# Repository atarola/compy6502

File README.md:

# compy6502

`compy6502` is an early-stage 6502 homebrew computer project. The long-term
goal is to build enough hardware and firmware to run Tetris on the machine.

The design follows the spirit of Ben Eater-style breadboard/modular 6502
systems for simplicity and debuggability, but uses a different memory map based
on the MMU/address-decoder architecture in `docs/mmu.png`.

The repo currently includes KiCad hardware designs, early ROM bring-up
firmware, build/write scripts, emulator test scaffolding, and architecture
reference images in `docs/`.

## Memory Map

The intended memory map is:

```text
$0000-$BFFF  RAM
$C000-$C0FF  I/O page
$C100-$FFFF  ROM
```

The I/O page is split into four 64-byte device slots:

```text
$C000-$C03F  IO0B
$C040-$C07F  IO1B
$C080-$C0BF  IO2B
$C0C0-$C0FF  IO3B
```

The linker script currently uses `$8000-$FFFF` as the 32 KB EEPROM image range
so CPU addresses map directly to the correct physical offsets on the chip.

## ROM Layout

The intended ROM organization is:

```text
$C100-$C1FF  public jump table
$C200-$DFFF  kernel routines and drivers
$E000-$EFFF  enhanced monitor
$F500-$FFF9  Wozmon fallback monitor
$FFFA-$FFFF  CPU vectors
```

## Credits

- `docs/mmu.png`: Mike McLaren, K8LH.
- `docs/Beater 02b.png`: Mike McLaren, K8LH.

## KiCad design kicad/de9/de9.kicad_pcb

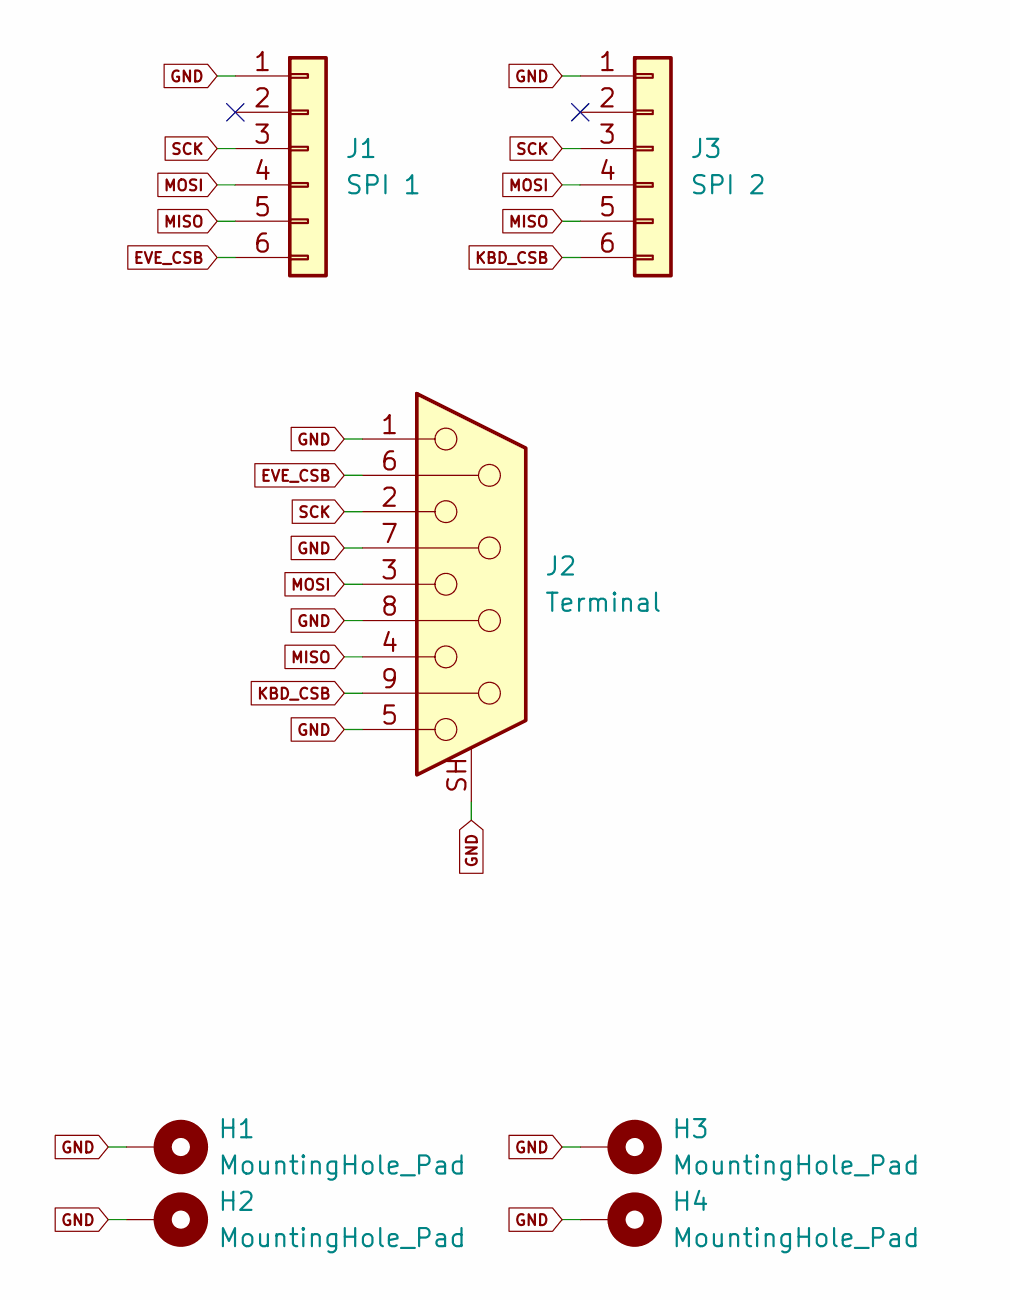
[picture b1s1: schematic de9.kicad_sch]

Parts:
H1, H2, H3, H4: MountingHole_Pad; MountingHole_2.2mm_M2_Pad
J1: SPI 1; JST_XH_B6B-XH-AM_1x06_P2.50mm_Vertical
J2: Terminal; DSUB-9_Pins_Horizontal_P2.77x2.84mm_EdgePinOffset4.94mm_Hou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
J3: SPI 2; JST_XH_B6B-XH-AM_1x06_P2.50mm_Vertical

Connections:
EVE_CSB: J1.6, J2.6
GND: H1.1 (1_1), H2.1 (1_1), H3.1 (1_1), H4.1 (1_1), J1.1, J2.1, J2.5, J2.7, J2.8, J2.SH (PAD), J3.1
KBD_CSB: J2.9, J3.6
MISO: J1.5, J2.4, J3.5
MOSI: J1.4, J2.3, J3.4
SCK: J1.3, J2.2, J3.3

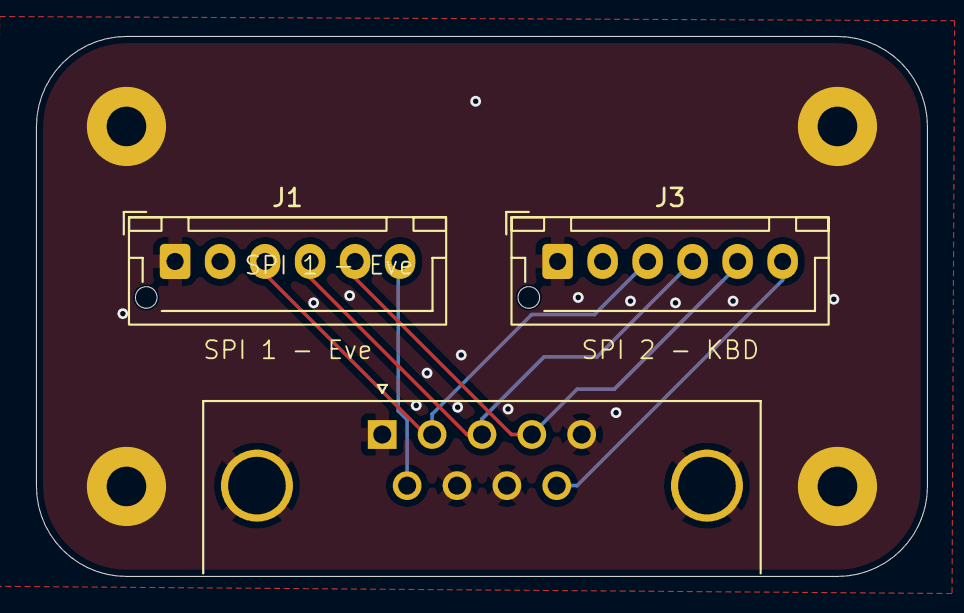
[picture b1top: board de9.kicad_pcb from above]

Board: 2 copper layers, 49.5 x 30.0 mm, 7 parts (0 on the bottom side), 6 nets.

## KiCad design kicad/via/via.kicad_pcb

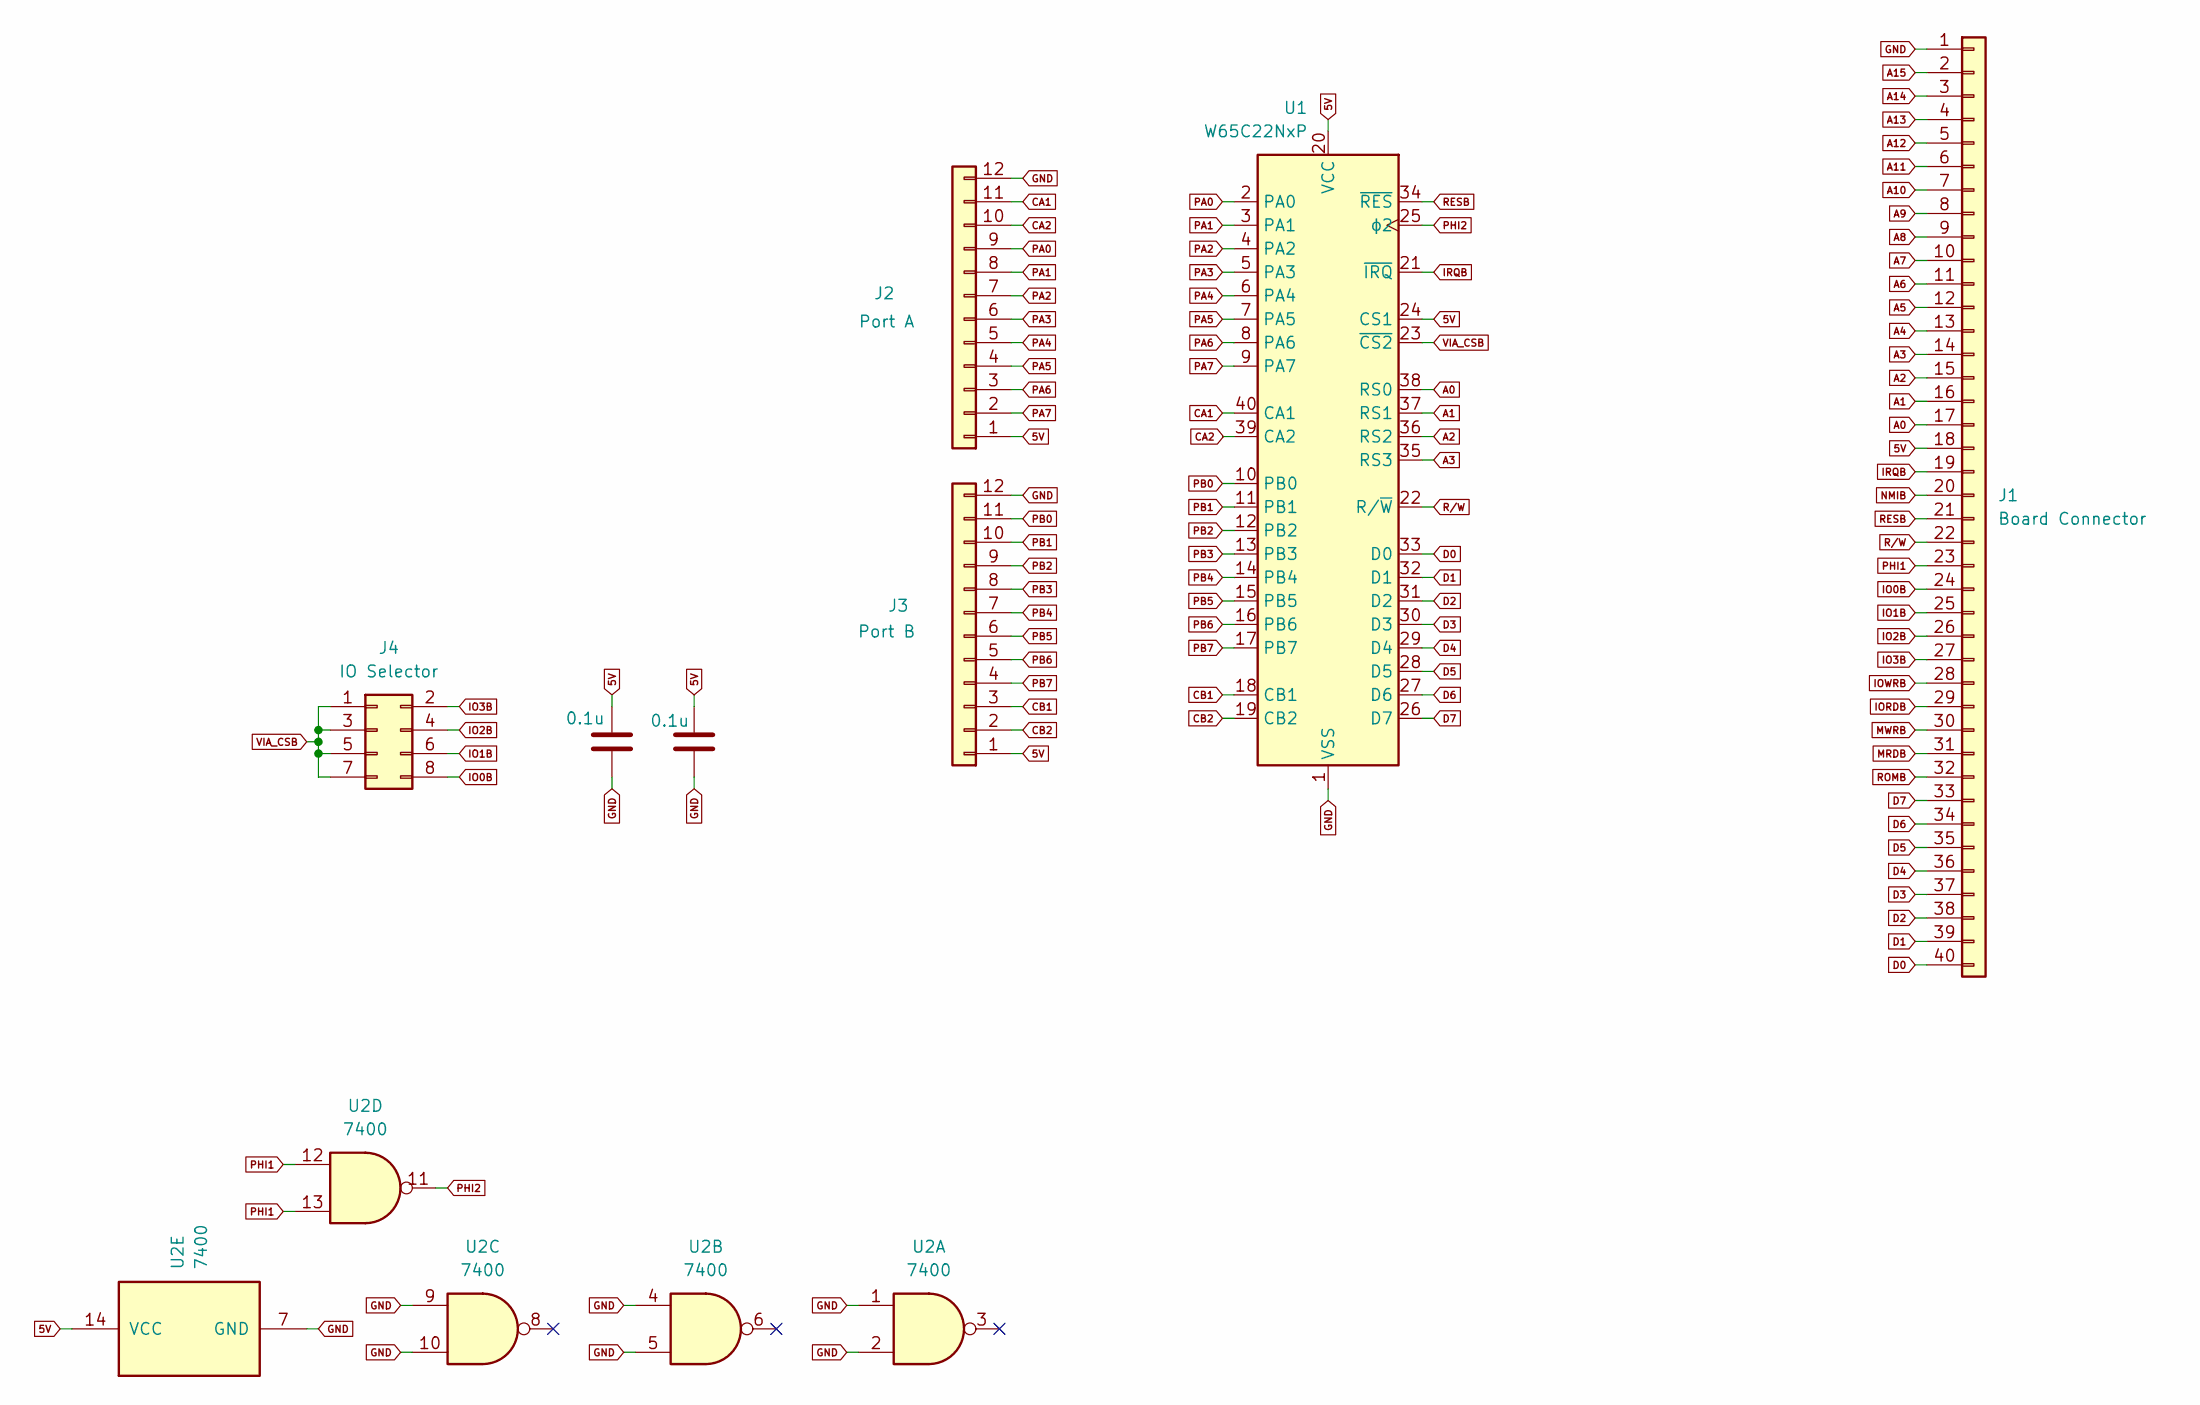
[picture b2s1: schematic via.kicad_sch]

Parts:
C1, C2: 0.1u; C_Disc_D3.0mm_W1.6mm_P2.50mm
J1: Board Connector; PinHeader_1x40_P2.54mm_Horizontal
J2: Port A; PinHeader_1x12_P2.00mm_Horizontal
J3: Port B; PinHeader_1x12_P2.00mm_Horizontal
J4: IO Selector; PinHeader_2x04_P2.54mm_Vertical
U1: W65C22NxP; DIP-40_W15.24mm_Socket_LongPads
U2: 7400; DIP-14_W7.62mm_Socket_LongPads

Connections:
5V: C1.1, C2.1, J1.18, J2.1, J3.1, U1.20 (VCC), U1.24 (CS1), U2.14 (VCC)
A0: J1.17, U1.38 (RS0)
A1: J1.16, U1.37 (RS1)
A2: J1.15, U1.36 (RS2)
A3: J1.14, U1.35 (RS3)
A4: J1.13
A5: J1.12
A6: J1.11
A7: J1.10
A8: J1.9
A9: J1.8
A10: J1.7
A11: J1.6
A12: J1.5
A13: J1.4
A14: J1.3
A15: J1.2
CA1: J2.11, U1.40 (CA1)
CA2: J2.10, U1.39 (CA2)
CB1: J3.3, U1.18 (CB1)
CB2: J3.2, U1.19 (CB2)
D0: J1.40, U1.33 (D0)
D1: J1.39, U1.32 (D1)
D2: J1.38, U1.31 (D2)
D3: J1.37, U1.30 (D3)
D4: J1.36, U1.29 (D4)
D5: J1.35, U1.28 (D5)
D6: J1.34, U1.27 (D6)
D7: J1.33, U1.26 (D7)
GND: C1.2, C2.2, J1.1, J2.12, J3.12, U1.1 (VSS), U2.1, U2.2, U2.4, U2.5, U2.7 (GND), U2.9, U2.10
IO0B: J1.24, J4.8
IO1B: J1.25, J4.6
IO2B: J1.26, J4.4
IO3B: J1.27, J4.2
IORDB: J1.29
IOWRB: J1.28
IRQB: J1.19, U1.21 (~IRQ)
MRDB: J1.31
MWRB: J1.30
NMIB: J1.20
PA0: J2.9, U1.2 (PA0)
PA1: J2.8, U1.3 (PA1)
PA2: J2.7, U1.4 (PA2)
PA3: J2.6, U1.5 (PA3)
PA4: J2.5, U1.6 (PA4)
PA5: J2.4, U1.7 (PA5)
PA6: J2.3, U1.8 (PA6)
PA7: J2.2, U1.9 (PA7)
PB0: J3.11, U1.10 (PB0)
PB1: J3.10, U1.11 (PB1)
PB2: J3.9, U1.12 (PB2)
PB3: J3.8, U1.13 (PB3)
PB4: J3.7, U1.14 (PB4)
PB5: J3.6, U1.15 (PB5)
PB6: J3.5, U1.16 (PB6)
PB7: J3.4, U1.17 (PB7)
PHI1: J1.23, U2.12, U2.13
PHI2: U1.25 (ϕ2), U2.11
RESB: J1.21, U1.34 (~RES)
ROMB: J1.32
R/W: J1.22, U1.22 (R/~W)
VIA_CSB: J4.1, J4.3, J4.5, J4.7, U1.23 (~CS2)

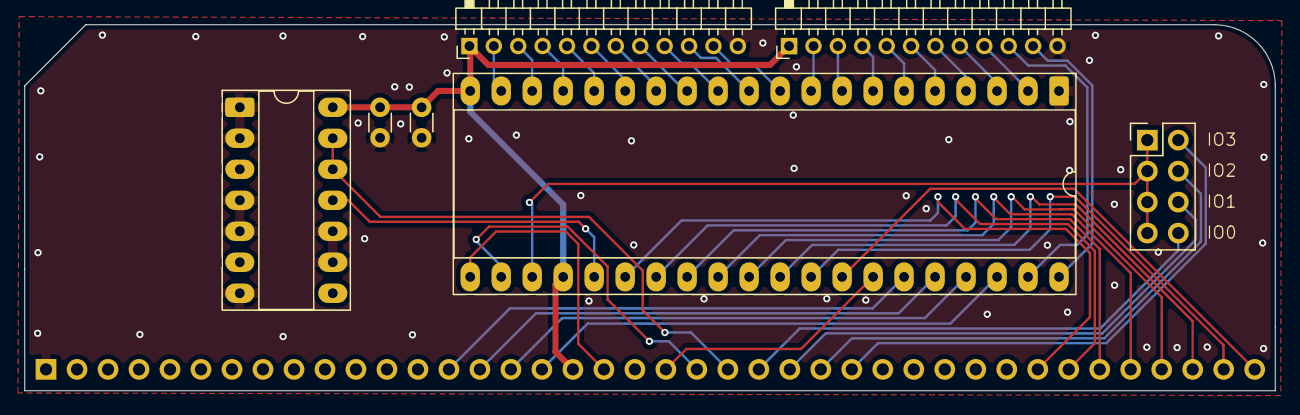
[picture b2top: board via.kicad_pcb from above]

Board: 2 copper layers, 102.5 x 30.0 mm, 8 parts (1 on the bottom side), 44 nets.

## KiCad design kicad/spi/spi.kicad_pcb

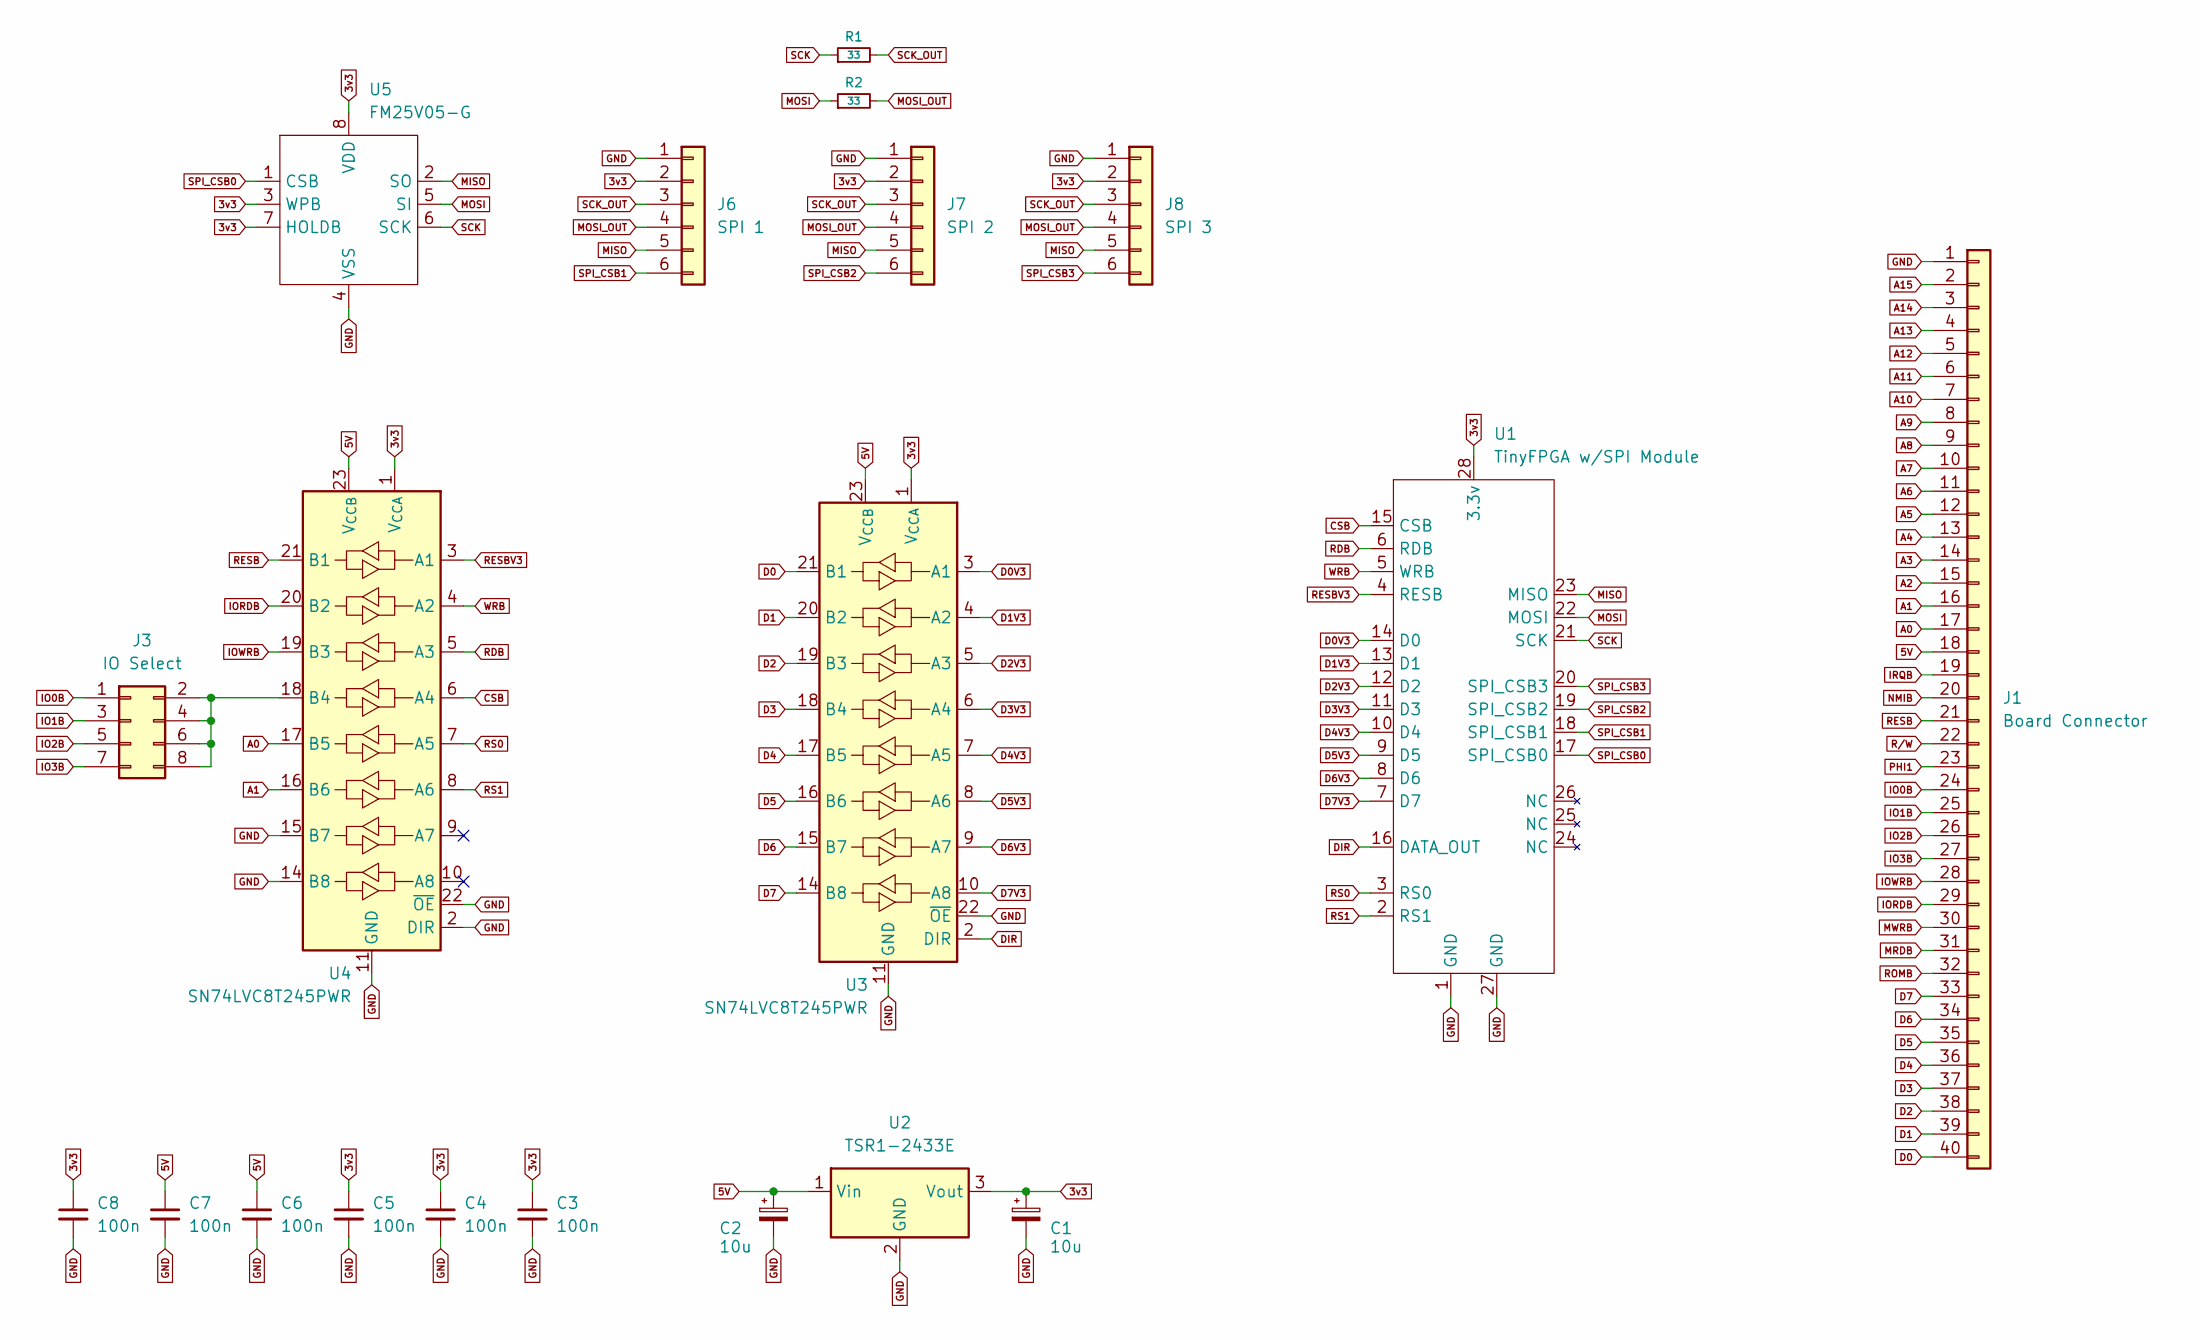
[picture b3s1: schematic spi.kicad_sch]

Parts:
C1, C2: 10u; C_1206_3216Metric
C3, C4, C5, C6, C7, C8: 100n; C_0603_1608Metric
J1: Board Connector; PinHeader_1x40_P2.54mm_Horizontal
J3: IO Select; PinHeader_2x04_P2.54mm_Vertical
J6: SPI 1; JST_XH_B6B-XH-AM_1x06_P2.50mm_Vertical
J7: SPI 2; JST_XH_B6B-XH-AM_1x06_P2.50mm_Vertical
J8: SPI 3; JST_XH_B6B-XH-AM_1x06_P2.50mm_Vertical
R1, R2: 33; R_0603_1608Metric
U1: TinyFPGA w/SPI Module; DIP-28_W15.24mm_Socket_LongPads
U2: TSR1-2433E; Converter_DCDC_TRACO_TSR1-xxxxE_THT
U3, U4: SN74LVC8T245PWR; TSSOP-24_4.4x7.8mm_P0.65mm
U5: FM25V05-G; SOIC-8_3.9x4.9mm_P1.27mm

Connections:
3v3: C1.1, C3.1, C4.1, C5.1, C8.1, J6.2, J7.2, J8.2, U1.28 (3.3v), U2.3 (Vout), U3.1 (V_{CCA}), U4.1 (V_{CCA}), U5.3 (WPB), U5.7 (HOLDB), U5.8 (VDD)
5V: C2.1, C6.1, C7.1, J1.18, U2.1 (Vin), U3.23 (V_{CCB}), U3.24 (V_{CCB}), U4.23 (V_{CCB}), U4.24 (V_{CCB})
A0: J1.17, U4.17 (B5)
A1: J1.16, U4.16 (B6)
A2: J1.15
A3: J1.14
A4: J1.13
A5: J1.12
A6: J1.11
A7: J1.10
A8: J1.9
A9: J1.8
A10: J1.7
A11: J1.6
A12: J1.5
A13: J1.4
A14: J1.3
A15: J1.2
CSB: U1.15 (CSB), U4.6 (A4)
D0: J1.40, U3.21 (B1)
D0V3: U1.14 (D0), U3.3 (A1)
D1: J1.39, U3.20 (B2)
D1V3: U1.13 (D1), U3.4 (A2)
D2: J1.38, U3.19 (B3)
D2V3: U1.12 (D2), U3.5 (A3)
D3: J1.37, U3.18 (B4)
D3V3: U1.11 (D3), U3.6 (A4)
D4: J1.36, U3.17 (B5)
D4V3: U1.10 (D4), U3.7 (A5)
D5: J1.35, U3.16 (B6)
D5V3: U1.9 (D5), U3.8 (A6)
D6: J1.34, U3.15 (B7)
D6V3: U1.8 (D6), U3.9 (A7)
D7: J1.33, U3.14 (B8)
D7V3: U1.7 (D7), U3.10 (A8)
DIR: U1.16 (DATA_OUT), U3.2 (DIR)
GND: C1.2, C2.2, C3.2, C4.2, C5.2, C6.2, C7.2, C8.2, J1.1, J6.1, J7.1, J8.1, U1.1 (GND), U1.27 (GND), U2.2 (GND), U3.11 (GND), U3.12 (GND), U3.13 (GND), U3.22 (~OE), U4.2 (DIR), U4.11 (GND), U4.12 (GND), U4.13 (GND), U4.14 (B8), U4.15 (B7), U4.22 (~OE), U5.4 (VSS)
IO0B: J1.24, J3.1
IO1B: J1.25, J3.3
IO2B: J1.26, J3.5
IO3B: J1.27, J3.7
IORDB: J1.29, U4.20 (B2)
IOWRB: J1.28, U4.19 (B3)
IRQB: J1.19
MISO: J6.5, J7.5, J8.5, U1.23 (MISO), U5.2 (SO)
MOSI: R2.1, U1.22 (MOSI), U5.5 (SI)
MOSI_OUT: J6.4, J7.4, J8.4, R2.2
MRDB: J1.31
MWRB: J1.30
NMIB: J1.20
unnamed: J3.2, J3.4, J3.6, J3.8, U4.18 (B4)
PHI1: J1.23
RDB: U1.6 (RDB), U4.5 (A3)
RESB: J1.21, U4.21 (B1)
RESBV3: U1.4 (RESB), U4.3 (A1)
ROMB: J1.32
RS0: U1.3 (RS0), U4.7 (A5)
RS1: U1.2 (RS1), U4.8 (A6)
R/W: J1.22
SCK: R1.1, U1.21 (SCK), U5.6 (SCK)
SCK_OUT: J6.3, J7.3, J8.3, R1.2
SPI_CSB0: U1.17 (SPI_CSB0), U5.1 (CSB)
SPI_CSB1: J6.6, U1.18 (SPI_CSB1)
SPI_CSB2: J7.6, U1.19 (SPI_CSB2)
SPI_CSB3: J8.6, U1.20 (SPI_CSB3)
WRB: U1.5 (WRB), U4.4 (A2)

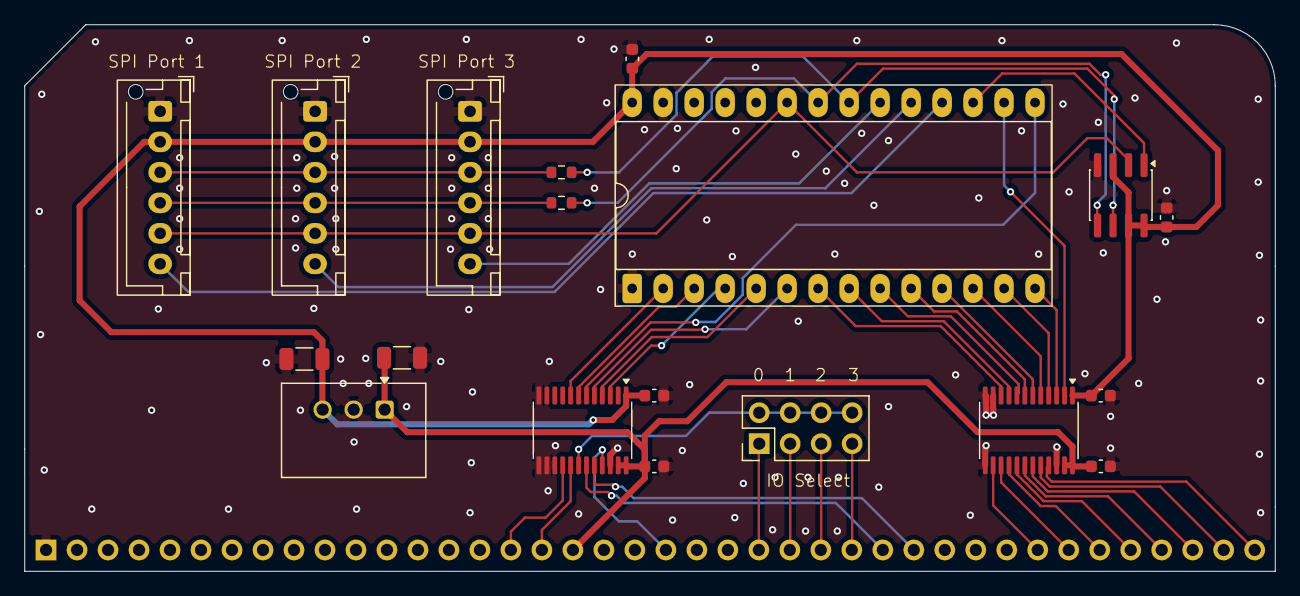
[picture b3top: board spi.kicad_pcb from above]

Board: 2 copper layers, 102.5 x 44.8 mm, 20 parts (1 on the bottom side), 45 nets.

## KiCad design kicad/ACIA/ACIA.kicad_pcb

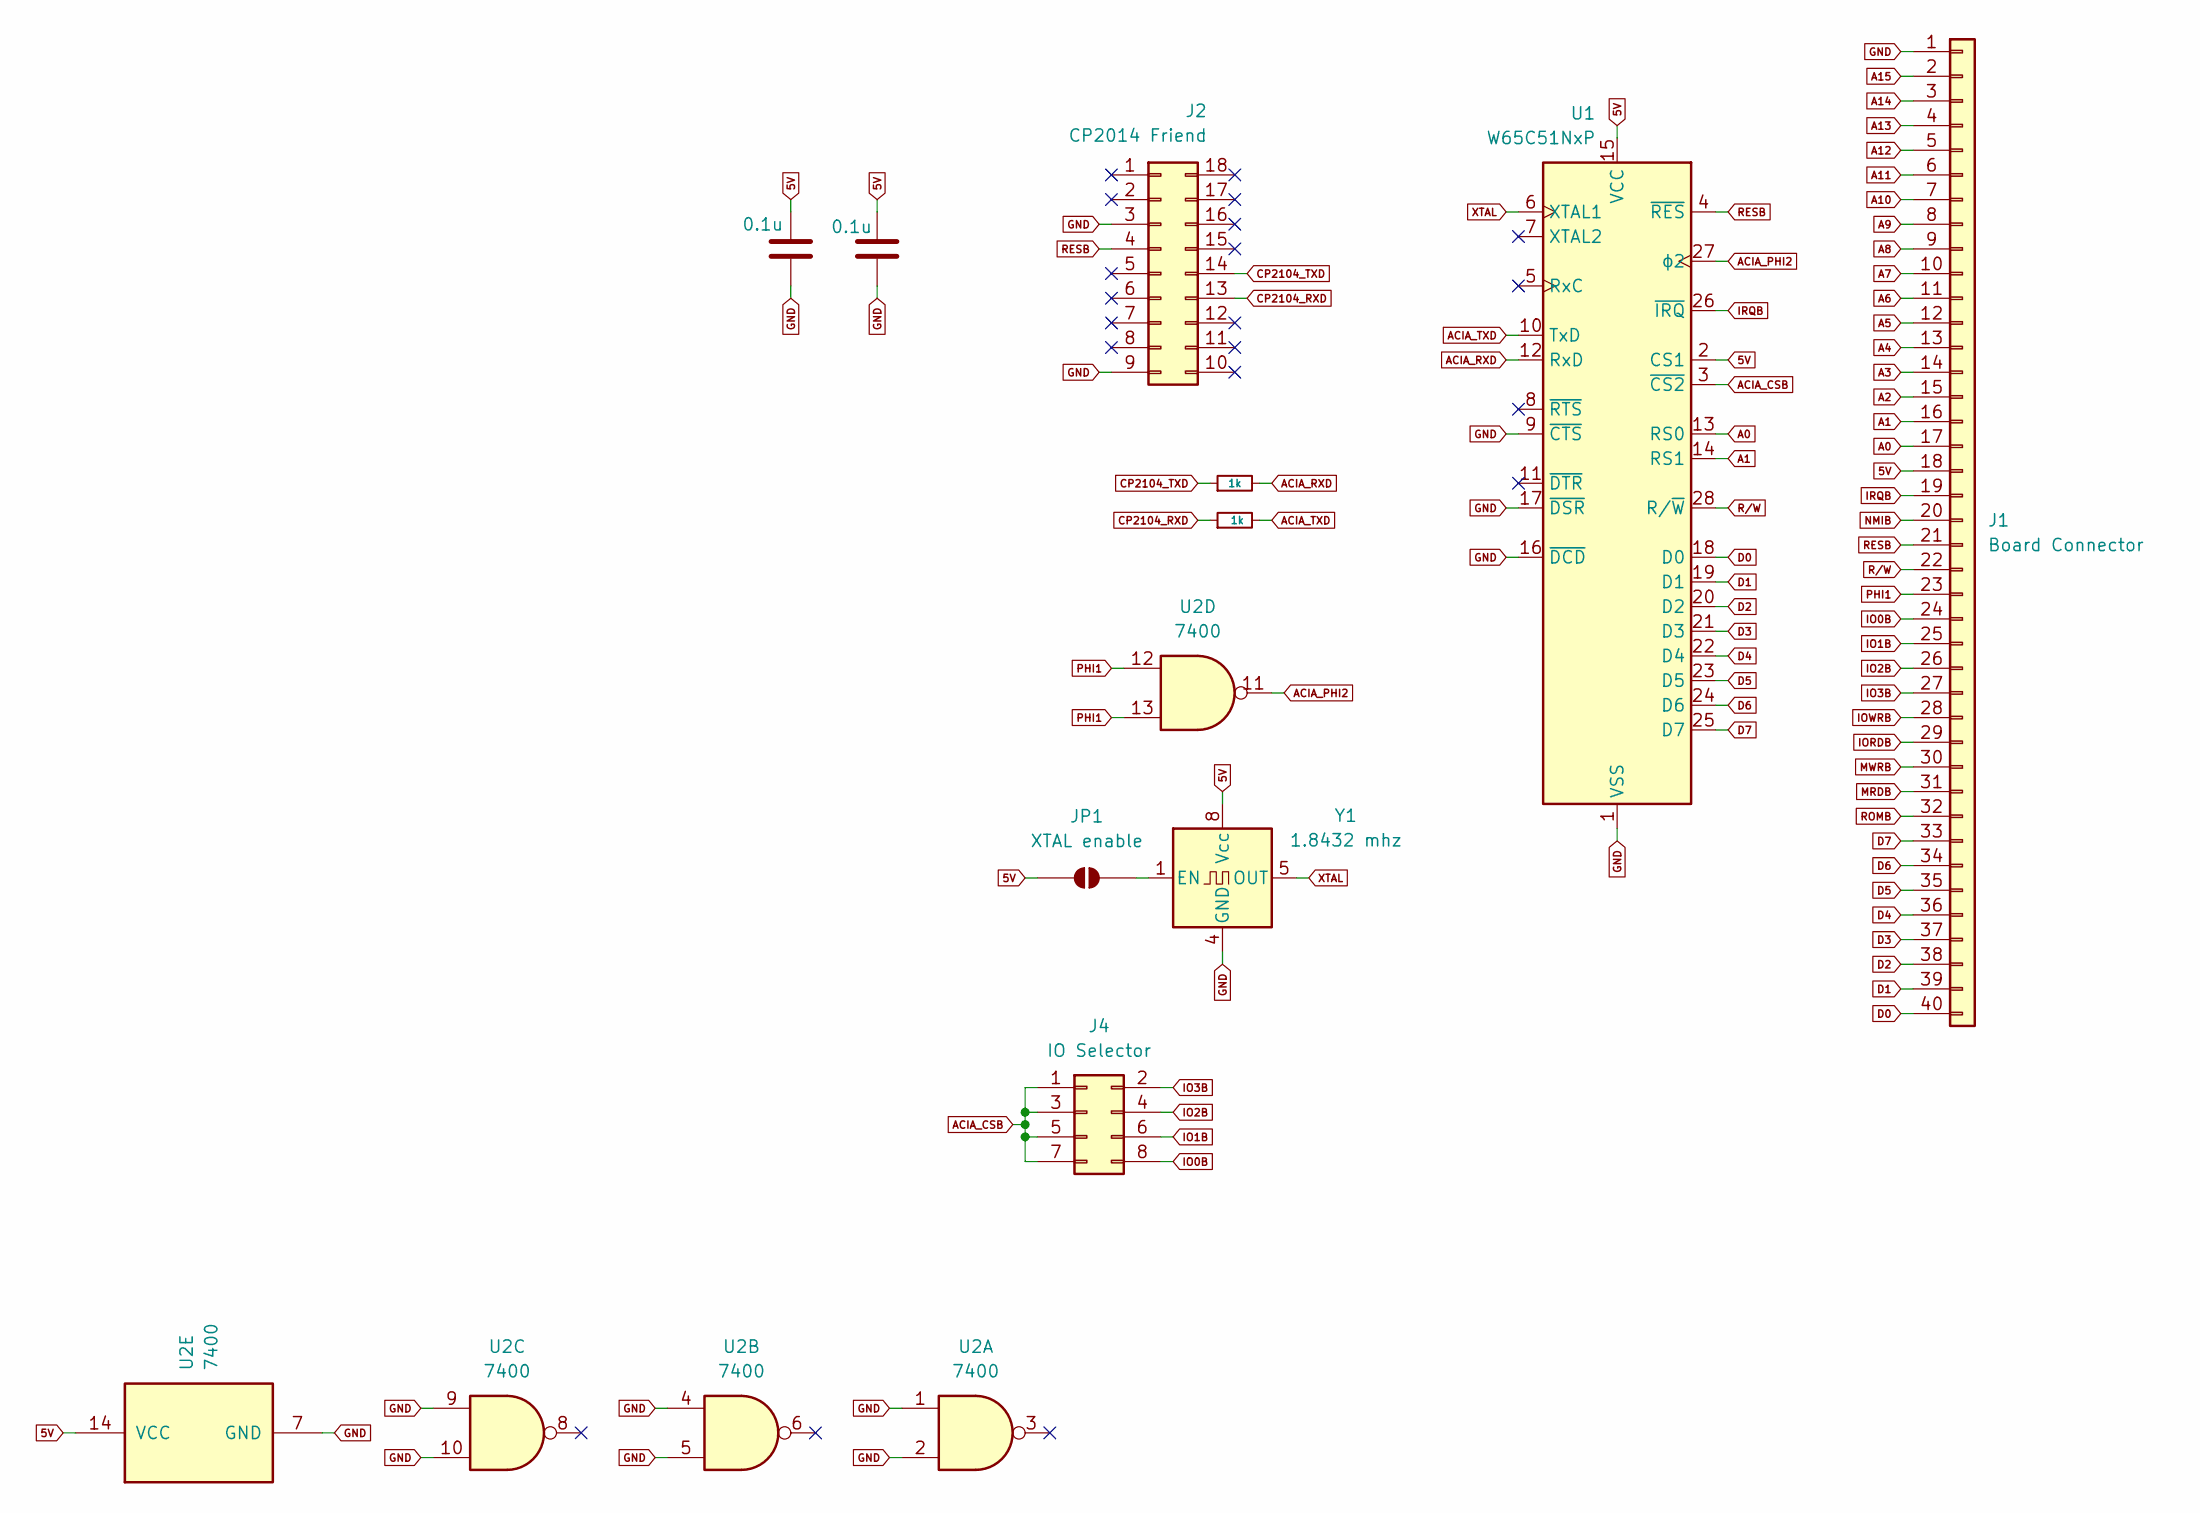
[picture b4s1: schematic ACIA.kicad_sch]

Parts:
C1, C2: 0.1u; C_Disc_D3.0mm_W1.6mm_P2.50mm
J1: Board Connector; PinHeader_1x40_P2.54mm_Horizontal
J2: CP2014 Friend; DIP-18_600_ELL
J4: IO Selector; PinHeader_2x04_P2.54mm_Vertical
JP1: XTAL enable; SolderJumper-2_P1.3mm_Open_TrianglePad1.0x1.5mm
R1, R2: 1k; R_Axial_DIN0207_L6.3mm_D2.5mm_P7.62mm_Horizontal
U1: W65C51NxP; DIP-28_W15.24mm_Socket_LongPads
U2: 7400; DIP-14_W7.62mm_Socket_LongPads
Y1: 1.8432 mhz; Oscillator_DIP-8

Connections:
5V: C1.1, C2.1, J1.18, JP1.1 (A), U1.2 (CS1), U1.15 (VCC), U2.14 (VCC), Y1.8 (Vcc)
A0: J1.17, U1.13 (RS0)
A1: J1.16, U1.14 (RS1)
A2: J1.15
A3: J1.14
A4: J1.13
A5: J1.12
A6: J1.11
A7: J1.10
A8: J1.9
A9: J1.8
A10: J1.7
A11: J1.6
A12: J1.5
A13: J1.4
A14: J1.3
A15: J1.2
ACIA_CSB: J4.1, J4.3, J4.5, J4.7, U1.3 (~CS2)
ACIA_PHI2: U1.27 (ϕ2), U2.11
ACIA_RXD: R1.2, U1.12 (RxD)
ACIA_TXD: R2.2, U1.10 (TxD)
CP2104_RXD: J2.13, R2.1
CP2104_TXD: J2.14, R1.1
D0: J1.40, U1.18 (D0)
D1: J1.39, U1.19 (D1)
D2: J1.38, U1.20 (D2)
D3: J1.37, U1.21 (D3)
D4: J1.36, U1.22 (D4)
D5: J1.35, U1.23 (D5)
D6: J1.34, U1.24 (D6)
D7: J1.33, U1.25 (D7)
GND: C1.2, C2.2, J1.1, J2.3, J2.9, U1.1 (VSS), U1.9 (~CTS), U1.16 (~DCD), U1.17 (~DSR), U2.1, U2.2, U2.4, U2.5, U2.7 (GND), U2.9, U2.10, Y1.4 (GND)
IO0B: J1.24, J4.8
IO1B: J1.25, J4.6
IO2B: J1.26, J4.4
IO3B: J1.27, J4.2
IORDB: J1.29
IOWRB: J1.28
IRQB: J1.19, U1.26 (~IRQ)
MRDB: J1.31
MWRB: J1.30
NMIB: J1.20
unnamed: JP1.2 (B), Y1.1 (EN)
PHI1: J1.23, U2.12, U2.13
RESB: J1.21, J2.4, U1.4 (~RES)
ROMB: J1.32
R/W: J1.22, U1.28 (R/~W)
XTAL: U1.6 (XTAL1), Y1.5 (OUT)

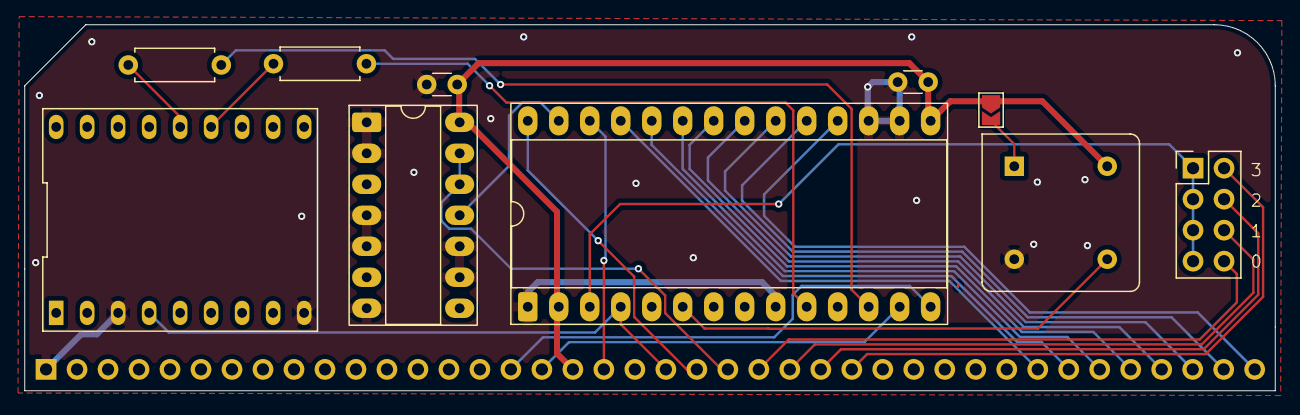
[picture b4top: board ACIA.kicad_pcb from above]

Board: 2 copper layers, 102.5 x 30.0 mm, 11 parts (1 on the bottom side), 28 nets.

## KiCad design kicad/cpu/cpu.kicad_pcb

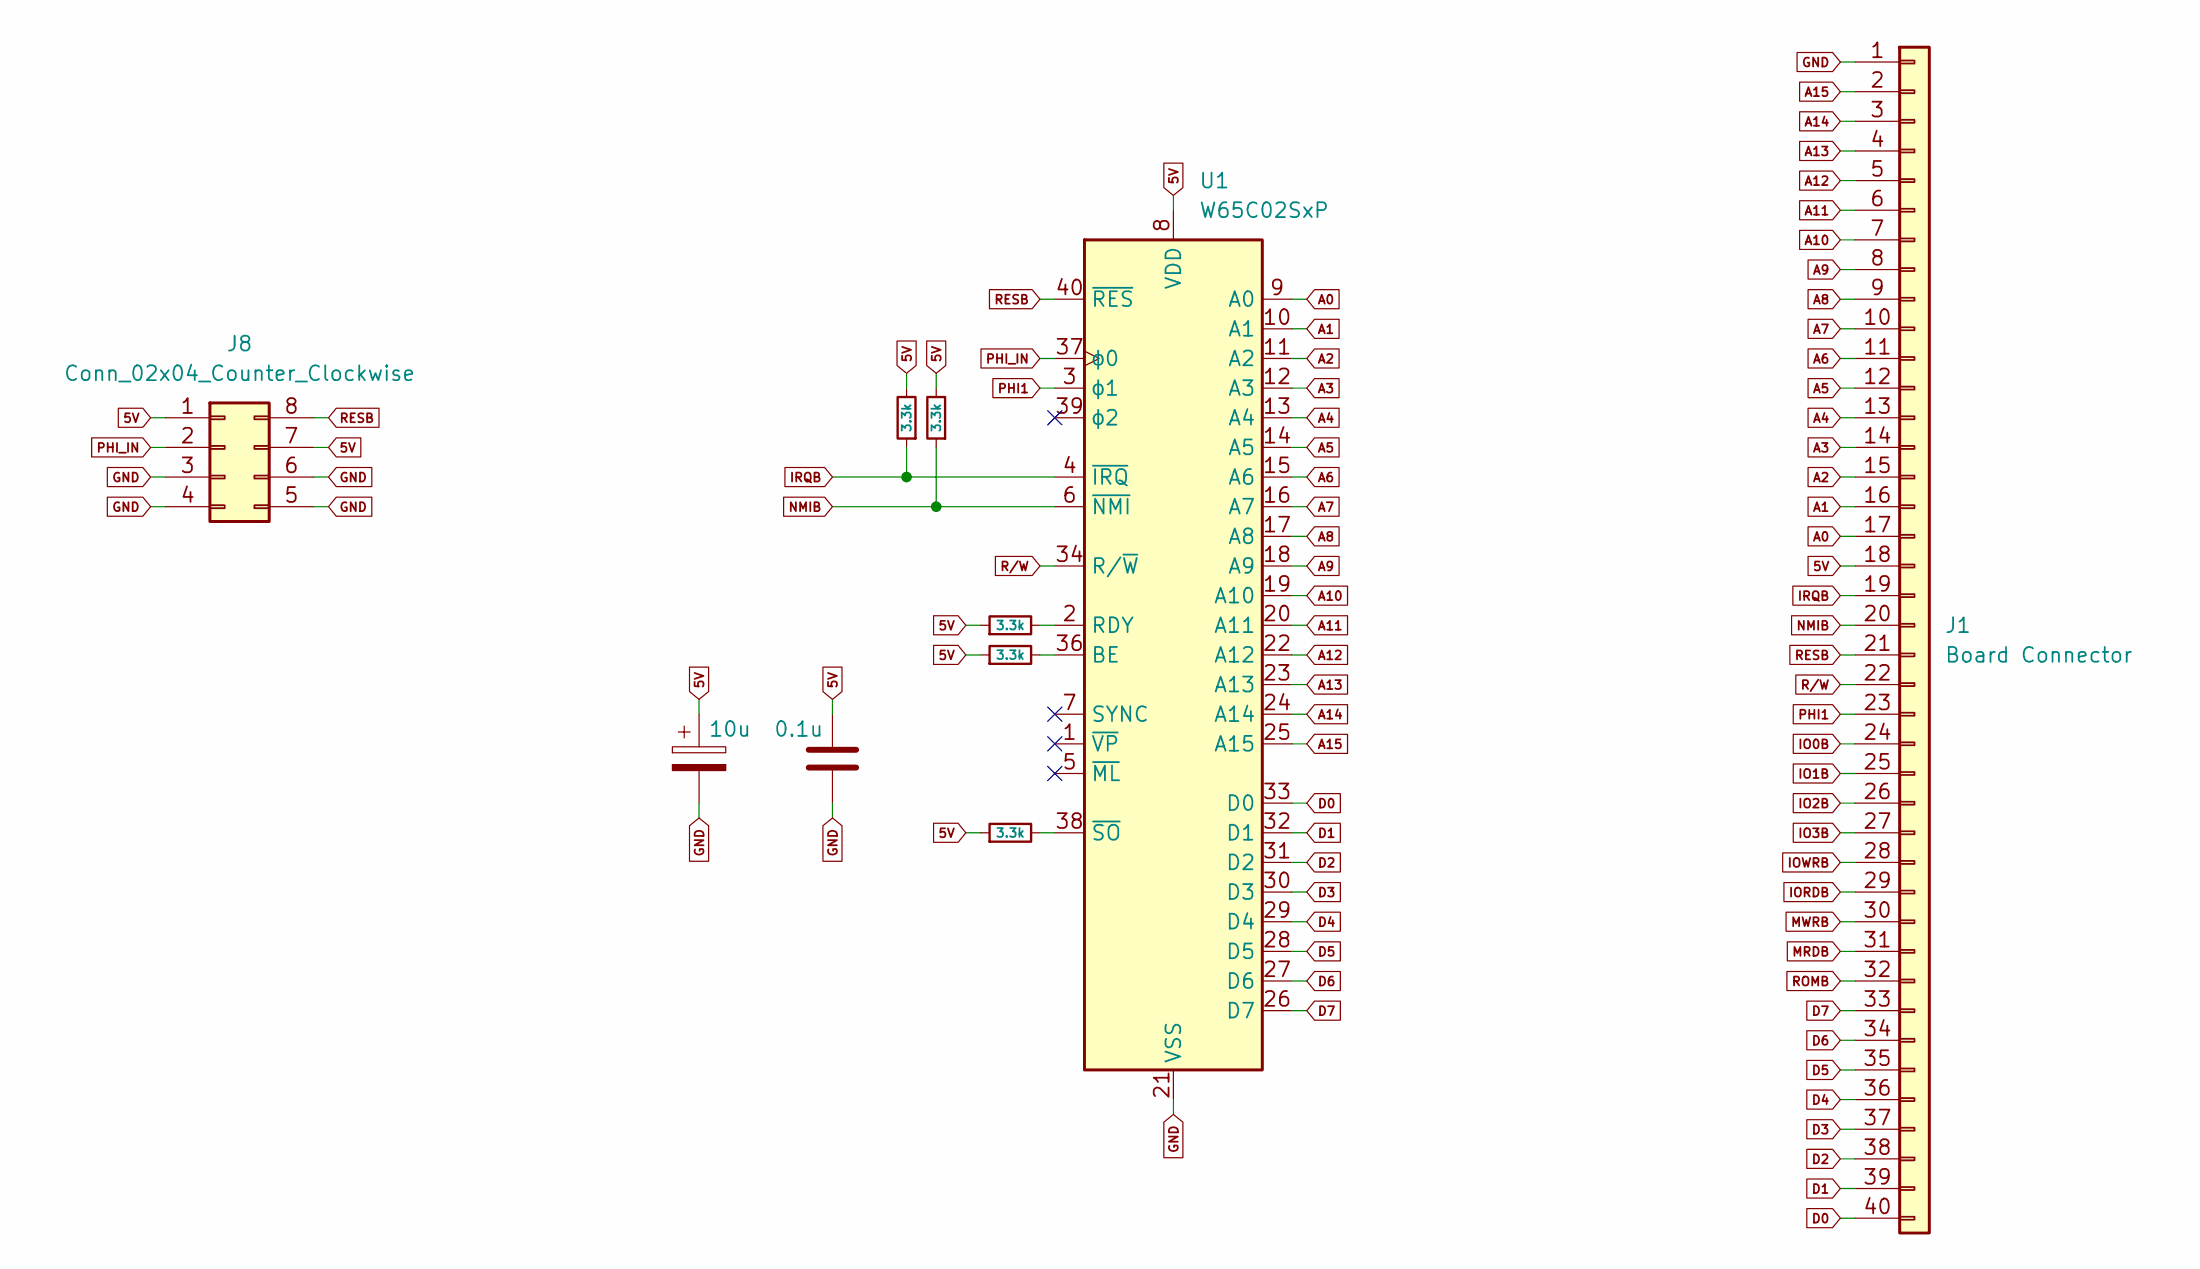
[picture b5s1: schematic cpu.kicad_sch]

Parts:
C1: 0.1u; C_Disc_D3.0mm_W1.6mm_P2.50mm
C3: 10u; CP_Radial_D5.0mm_P2.50mm
J1: Board Connector; PinHeader_1x40_P2.54mm_Horizontal
J8: Conn_02x04_Counter_Clockwise; PinHeader_2x04_P2.54mm_Horizontal
R1, R2, R3, R4, R5: 3.3k; R_Axial_DIN0207_L6.3mm_D2.5mm_P7.62mm_Horizontal
U1: W65C02SxP; DIP-40_W15.24mm_Socket

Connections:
5V: C1.1, C3.1, J1.18, J8.1, J8.7, R1.1, R2.1, R3.1, R4.2, R5.2, U1.8 (VDD)
A0: J1.17, U1.9 (A0)
A1: J1.16, U1.10 (A1)
A2: J1.15, U1.11 (A2)
A3: J1.14, U1.12 (A3)
A4: J1.13, U1.13 (A4)
A5: J1.12, U1.14 (A5)
A6: J1.11, U1.15 (A6)
A7: J1.10, U1.16 (A7)
A8: J1.9, U1.17 (A8)
A9: J1.8, U1.18 (A9)
A10: J1.7, U1.19 (A10)
A11: J1.6, U1.20 (A11)
A12: J1.5, U1.22 (A12)
A13: J1.4, U1.23 (A13)
A14: J1.3, U1.24 (A14)
A15: J1.2, U1.25 (A15)
D0: J1.40, U1.33 (D0)
D1: J1.39, U1.32 (D1)
D2: J1.38, U1.31 (D2)
D3: J1.37, U1.30 (D3)
D4: J1.36, U1.29 (D4)
D5: J1.35, U1.28 (D5)
D6: J1.34, U1.27 (D6)
D7: J1.33, U1.26 (D7)
GND: C1.2, C3.2, J1.1, J8.3, J8.4, J8.5, J8.6, U1.21 (VSS)
IO0B: J1.24
IO1B: J1.25
IO2B: J1.26
IO3B: J1.27
IORDB: J1.29
IOWRB: J1.28
IRQB: J1.19, R5.1, U1.4 (~IRQ)
MRDB: J1.31
MWRB: J1.30
NMIB: J1.20, R4.1, U1.6 (~NMI)
unnamed: R3.2, U1.36 (BE)
unnamed: R1.2, U1.2 (RDY)
unnamed: R2.2, U1.38 (~SO)
PHI1: J1.23, U1.3 (ϕ1)
PHI_IN: J8.2, U1.37 (ϕ0)
RESB: J1.21, J8.8, U1.40 (~RES)
ROMB: J1.32
R/W: J1.22, U1.34 (R/~W)

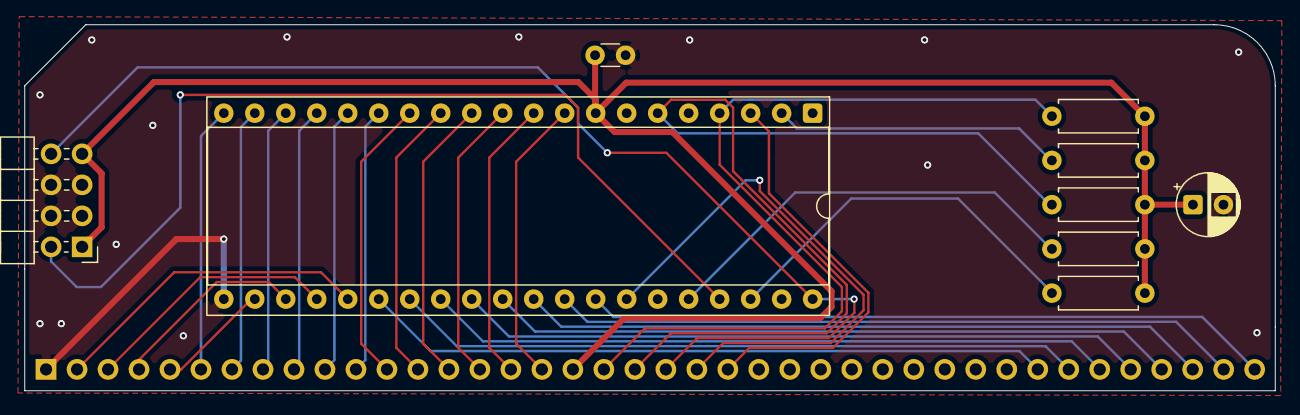
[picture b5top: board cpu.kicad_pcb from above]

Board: 2 copper layers, 102.5 x 30.0 mm, 10 parts (1 on the bottom side), 35 nets.
